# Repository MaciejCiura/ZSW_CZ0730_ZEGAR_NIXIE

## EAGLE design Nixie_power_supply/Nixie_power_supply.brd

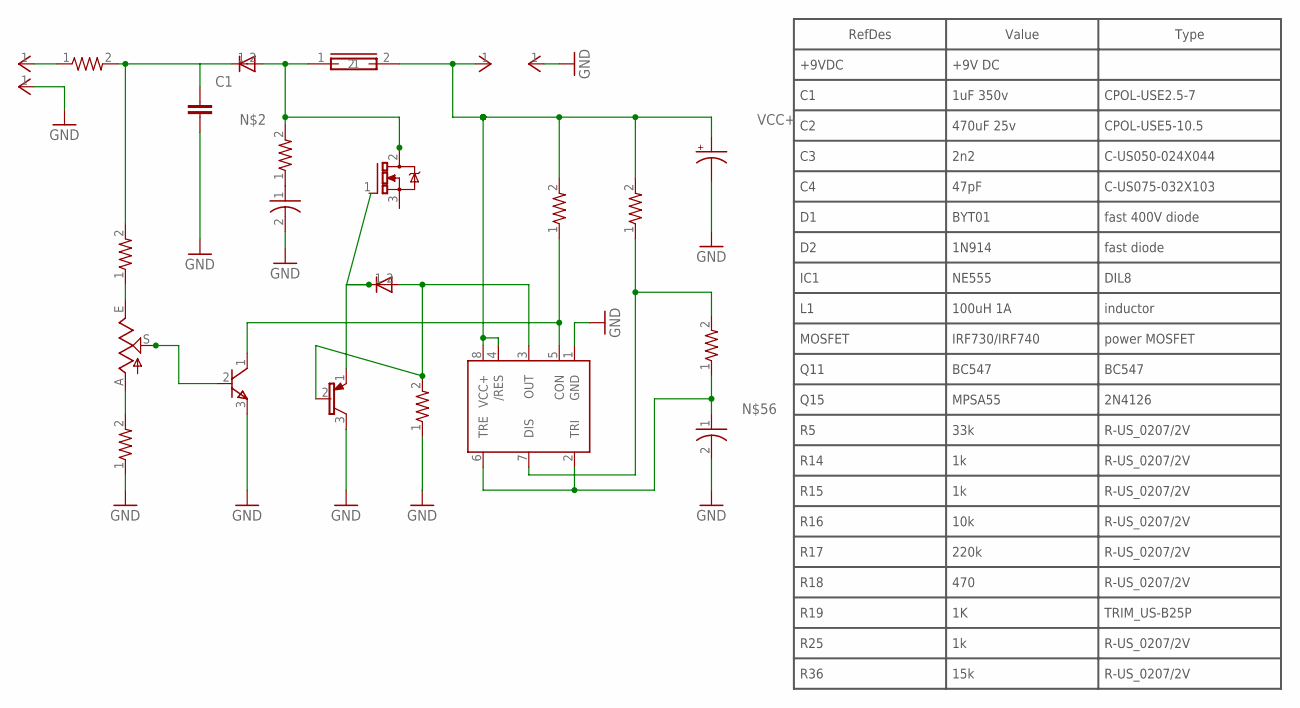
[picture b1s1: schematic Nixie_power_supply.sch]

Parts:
ANODE: 9V; 1PIN
C2: 470uF 25v; SANYO-OSCON_C6
C3: 2n2; CAP_CERAMIC_M
C4: 47pF; CAP_CERAMIC_M
CATHODE: 9V; 1PIN
D1: BYT01; DIODE_S
D2: 1N914; DIODE_ORIZZ_S
GND: 9V; 1PIN
IC1: NE555; DIL-08
L1: 100uH 1A; GENERIC_M
MOSFET: IRF730/IRF740; TO-220_VERT
Q11: BC547; TRANSISTOR_TO-92-100_L
Q15: MPSA55; TRANSISTOR_TO-92-100
R5: 33k; RES_ORIZZ_S
R14, R15, R25: 1k; RES_ORIZZ_S
R16: 10k; RES_ORIZZ_S
R17: 220k; RES_ORIZZ_S
R18: 470; RES_ORIZZ_S
R19: 1K; POT_QUAD_B25P
R36: 15k; RES_ORIZZ_S
VCC+: 9V; 1PIN

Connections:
GND: C2.-, C3.2, C4.2, CATHODE.1, GND.1, IC1.1 (GND), Q11.3 (E), Q15.3 (C), R18.1, R25.1
unnamed: D2.1 (C), MOSFET.1 (G), Q15.1 (E)
unnamed: D1.2 (A), L1.1, MOSFET.2 (D), R15.2
unnamed: D1.1 (C), R17.2, R36.2
unnamed: C4.1, R15.1
unnamed: R17.1, R19.E
unnamed: IC1.7 (DIS), R14.1, R16.2
unnamed: IC1.5 (CON), Q11.1 (C), R5.1
unnamed: C3.1, IC1.2 (TRI), IC1.6 (TRE), R16.1
NET_13: ANODE.1, R36.1
NET_65: R18.2, R19.A
NET_69: Q11.2 (B), R19.S
NET_71: D2.2 (A), IC1.3 (OUT), Q15.2 (B), R25.2
VCC+: C2.+, IC1.4 (/RES), IC1.8 (VCC+), L1.2, R5.2, R14.2, VCC+.1

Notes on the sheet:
RefDes
+9VDC
IC1
MOSFET
Q11
Q15
R14
R15
R16
R17
R18
R19
R25
R36
Value
+9V DC
1uF 350v
470uF 25v
2n2
47pF
BYT01
1N914
NE555
100uH 1A
IRF730/IRF740
BC547
MPSA55
33k
10k
220k
470
15k
Type
CPOL-USE2.5-7
CPOL-USE5-10.5
C-US050-024X044
C-US075-032X103
fast 400V diode
fast diode
DIL8

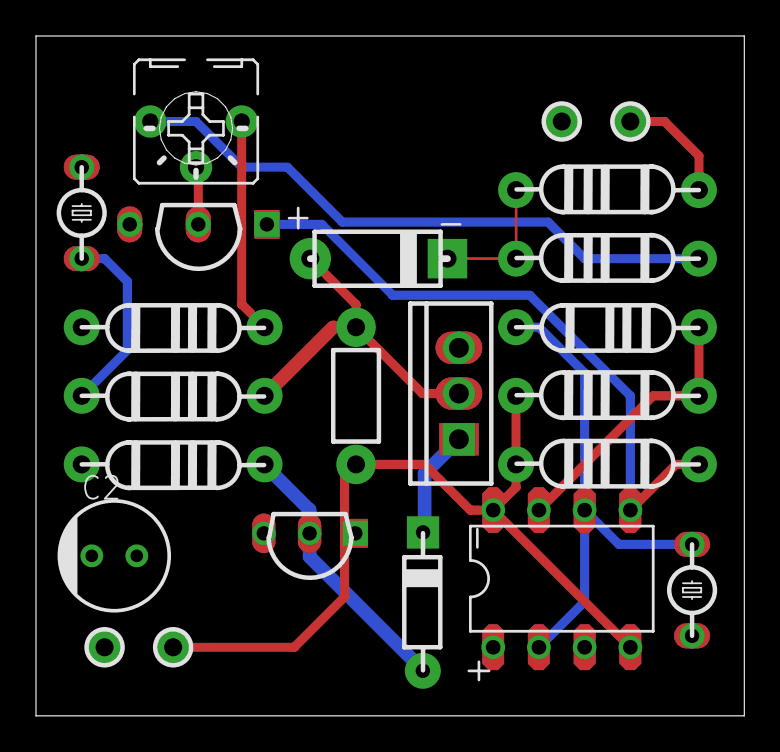
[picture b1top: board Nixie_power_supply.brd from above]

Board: 2 copper layers, 39.4 x 37.8 mm, 23 parts (0 on the bottom side), 14 nets.

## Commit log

2021-12-09 Final version
